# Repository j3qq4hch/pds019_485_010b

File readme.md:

# pds019_485_010

В этом репозитории содержатся исходники проекта `pds019_485_010`. Проект включает в себя две платы: A и B.

На плате А располагается модуль esp32, разъемы для его программирования две кнопки и несколько светодиодов.

На плате B располагается система питания устройства, состоящая из AC-DC модуля, создающего шину питания 12в и DC-DC конвертера 12в -> 3.3в. Кроме этого на плате B располагается гальванически изолированный RS485 интерфейс, реле и разъем для подключения датчика. 

# Плата А

# Плата B
<p align = center>

| Сторона TOP  | Сторона BOTTOM |
|-------------|-----------|
|||

</p>

3D модель доступна [по ссылке](https://a360.co/4bcfLyz).
BoM доступен [по ссылке](https://docs.google.com/spreadsheets/d/1rppHGotYg97vevn0TNhSlOjf3by5jG4KPH9rv6CT_tg/edit?gid=943701483#gid=943701483).

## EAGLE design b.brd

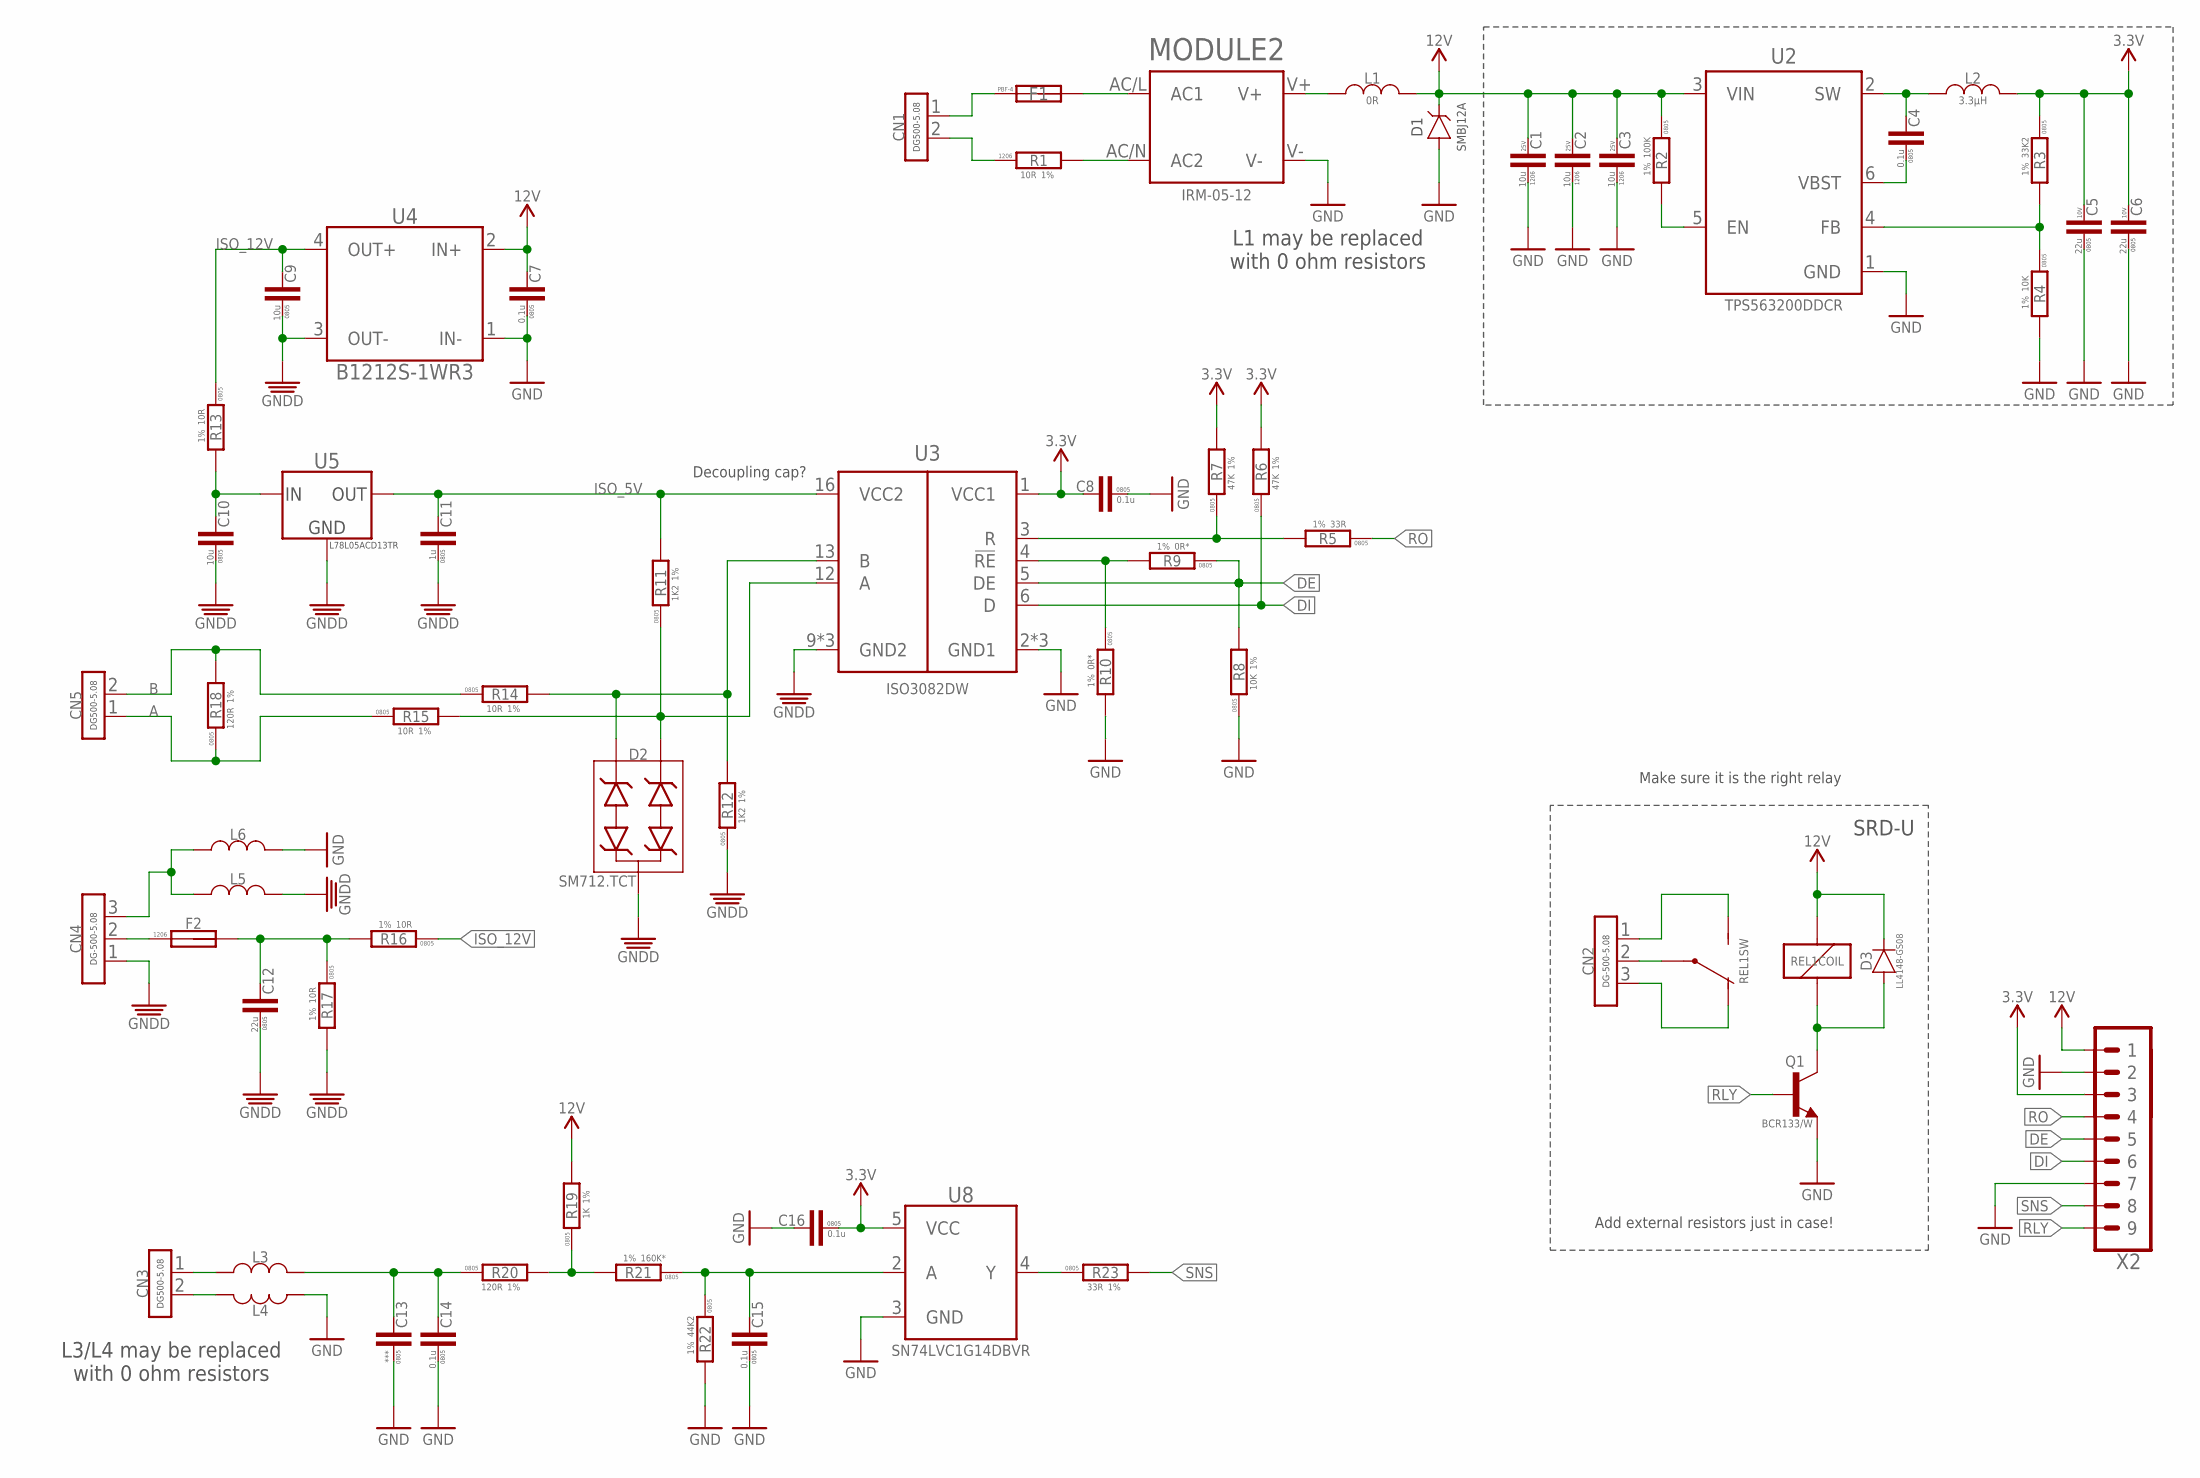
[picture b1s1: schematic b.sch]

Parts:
C1, C2, C3: 10u; C1206; VOLTAGE 25V
C4, C7, C8, C14, C15, C16: 0.1u; C0805
C5, C6: 22u; C0805; VOLTAGE 10V
C9, C10: 10u; C0805
C11: 1u; C0805
C12: 22u; C0805
C13: ***; C0805
CN1, CN3, CN5: CON-2P-DG500-5.08; DG500-5.08-02P
CN2, CN4: CON-3P-DG500-5.08; DG500-5.08-03P
D1: SMBJ12A-SMB; DO-214AA(SMB)
D2: SM712; SOT23B-3
D3: LL4148; LL-34
F1: 1.6A; MST-FUSE
F2: MF-NSMF050-2; F1206
L1: 0R; L0805
L2: 3.3µH; VLS6045EX
L3, L4, L5, L6: L-0805; L0805
MODULE2: IRM-05-12; IRM-05
Q1: BCR133; SOT23B-3
R1: 10R; R1206
R2: 100K; R0805
R3: 33K2; R0805
R4, R8: 10K; R0805
R5, R23: 33R; R0805
R6, R7: 47K; R0805
R9, R10: 0R*; R0805
R11, R12: 1K2; R0805
R13, R14, R15, R16, R17: 10R; R0805
R18, R20: 120R; R0805
R19: 1K; R0805
R21: 160K*; R0805
R22: 44K2; R0805
REL1: RELAY_SPDTHJR-3FF-SH; HJR-3FF-12VDC-S-Z
U2: TPS563200; SOT23-6
U3: ISO3082; SO-16W
U4: B1212S-1WR3; SIP-4
U5: L78L05ACD13TR; SOIC8
U8: 74LVC1G14DBV; SOT23-5
X2: PINHEAD_1X09-2.54-TH-MALE; 1X09-PTH-2.54

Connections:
3490587: R5.2, R7.1, U3.3 (R)
+12V: CN4.2, F2.P$1 (1)
A: CN5.1, R15.1, R18.1
B: CN5.2, R14.1, R18.2
DE: R8.2, R9.1, U3.5 (DE), X2.5
DI: R6.1, U3.6 (D), X2.6
GND: C1.P$1 (1), C2.P$1 (1), C3.P$1 (1), C5.1, C6.1, C7.1, C8.1, C13.1, C14.1, C15.1, C16.2, D1.A, L4.2, L6.1, MODULE2.V-, Q1.2 (E), R4.2, R8.1, R10.2, R22.2, U2.1 (GND), U3.2 (GND1), U3.7 (GND1), U3.8 (GND1), U4.1 (IN-), U8.3 (GND), X2.2, X2.7
GNDD: C9.1, C10.1, C11.1, C12.1, CN4.1, D2.3, L5.2, R12.1, R17.2, U3.9 (GND2), U3.10 (GND2), U3.15 (GND2), U4.3 (OUT-), U5.2 (GND), U5.3 (GND), U5.6 (GND), U5.7 (GND)
ISO_5V: C11.2, R11.2, U3.16 (VCC2), U5.1 (OUT)
ISO_12V: C9.2, R13.1, R16.1, U4.4 (OUT+)
unnamed: CN4.3, L5.1, L6.2
unnamed: MODULE2.AC/N (AC2), R1.P$2 (2)
unnamed: D2.2 (C2), R11.1, R15.2, U3.12 (A)
unnamed: D2.1 (C3), R12.2, R14.2, U3.13 (B)
unnamed: F1.2, MODULE2.AC/L (AC1)
unnamed: L1.1, MODULE2.V+
unnamed: C4.1, U2.6 (VBST)
unnamed: R9.2, R10.1, U3.4 (!RE)
unnamed: CN1.1, F1.1
unnamed: CN1.2, R1.P$1 (1)
unnamed: R2.2, U2.5 (EN)
unnamed: C4.2, L2.P$1 (1), U2.2 (SW)
unnamed: R3.2, R4.1, U2.4 (FB)
unnamed: CN2.2, REL1.1 (COM)
unnamed: CN2.3, REL1.4 (NC)
unnamed: CN2.1, REL1.3 (NO)
unnamed: CN3.1, L3.1
unnamed: CN3.2, L4.1
unnamed: C13.2, C14.2, L3.2, R20.1
unnamed: C10.2, R13.2, U5.8 (IN)
unnamed: R19.1, R20.2, R21.2
unnamed: C15.2, R21.1, R22.1, U8.2 (A)
unnamed: D3.A, Q1.3 (C), REL1.5 (2)
unnamed: R23.1, U8.4 (Y)
unnamed: C12.2, F2.P$2 (2), R16.2, R17.1
RLY: Q1.1 (B), X2.9
RO: R5.1, X2.4
SNS: R23.2, X2.8
VDD_3V3: C5.2, C6.2, C8.2, C16.1, L2.P$2 (2), R3.1, R6.2, R7.2, U3.1 (VCC1), U8.5 (VCC), X2.3
VDD_12V: C1.P$2 (2), C2.P$2 (2), C3.P$2 (2), C7.2, D1.C, D3.C, L1.2, R2.1, R19.2, REL1.2 (1), U2.3 (VIN), U4.2 (IN+), X2.1

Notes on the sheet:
Add external resistors just in case!
Make sure it is the right relay
Decoupling cap?
SRD-U
L3/L4 may be replaced with 0 ohm resistors
L1 may be replaced with 0 ohm resistors

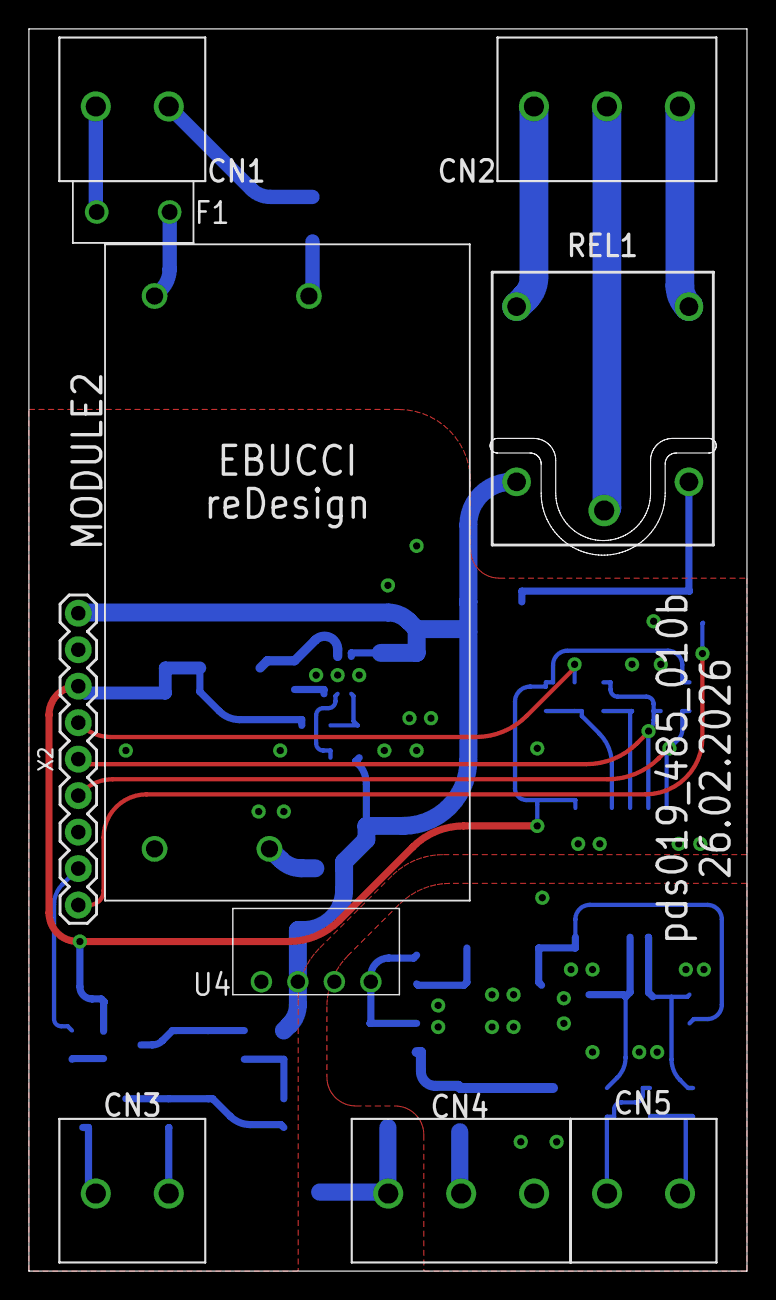
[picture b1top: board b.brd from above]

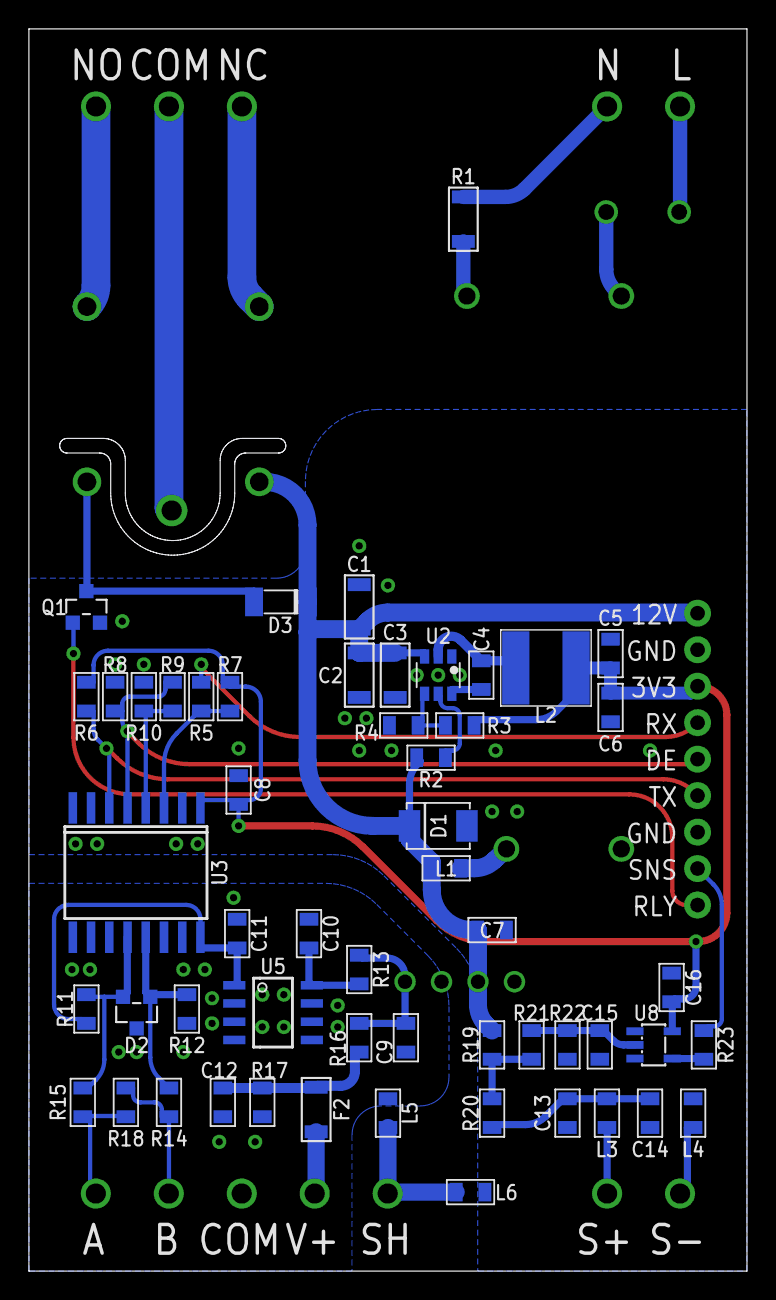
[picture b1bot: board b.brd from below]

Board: 2 copper layers, 50.0 x 86.5 mm, 65 parts (54 on the bottom side), 40 nets.

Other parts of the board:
U$1: REF_B

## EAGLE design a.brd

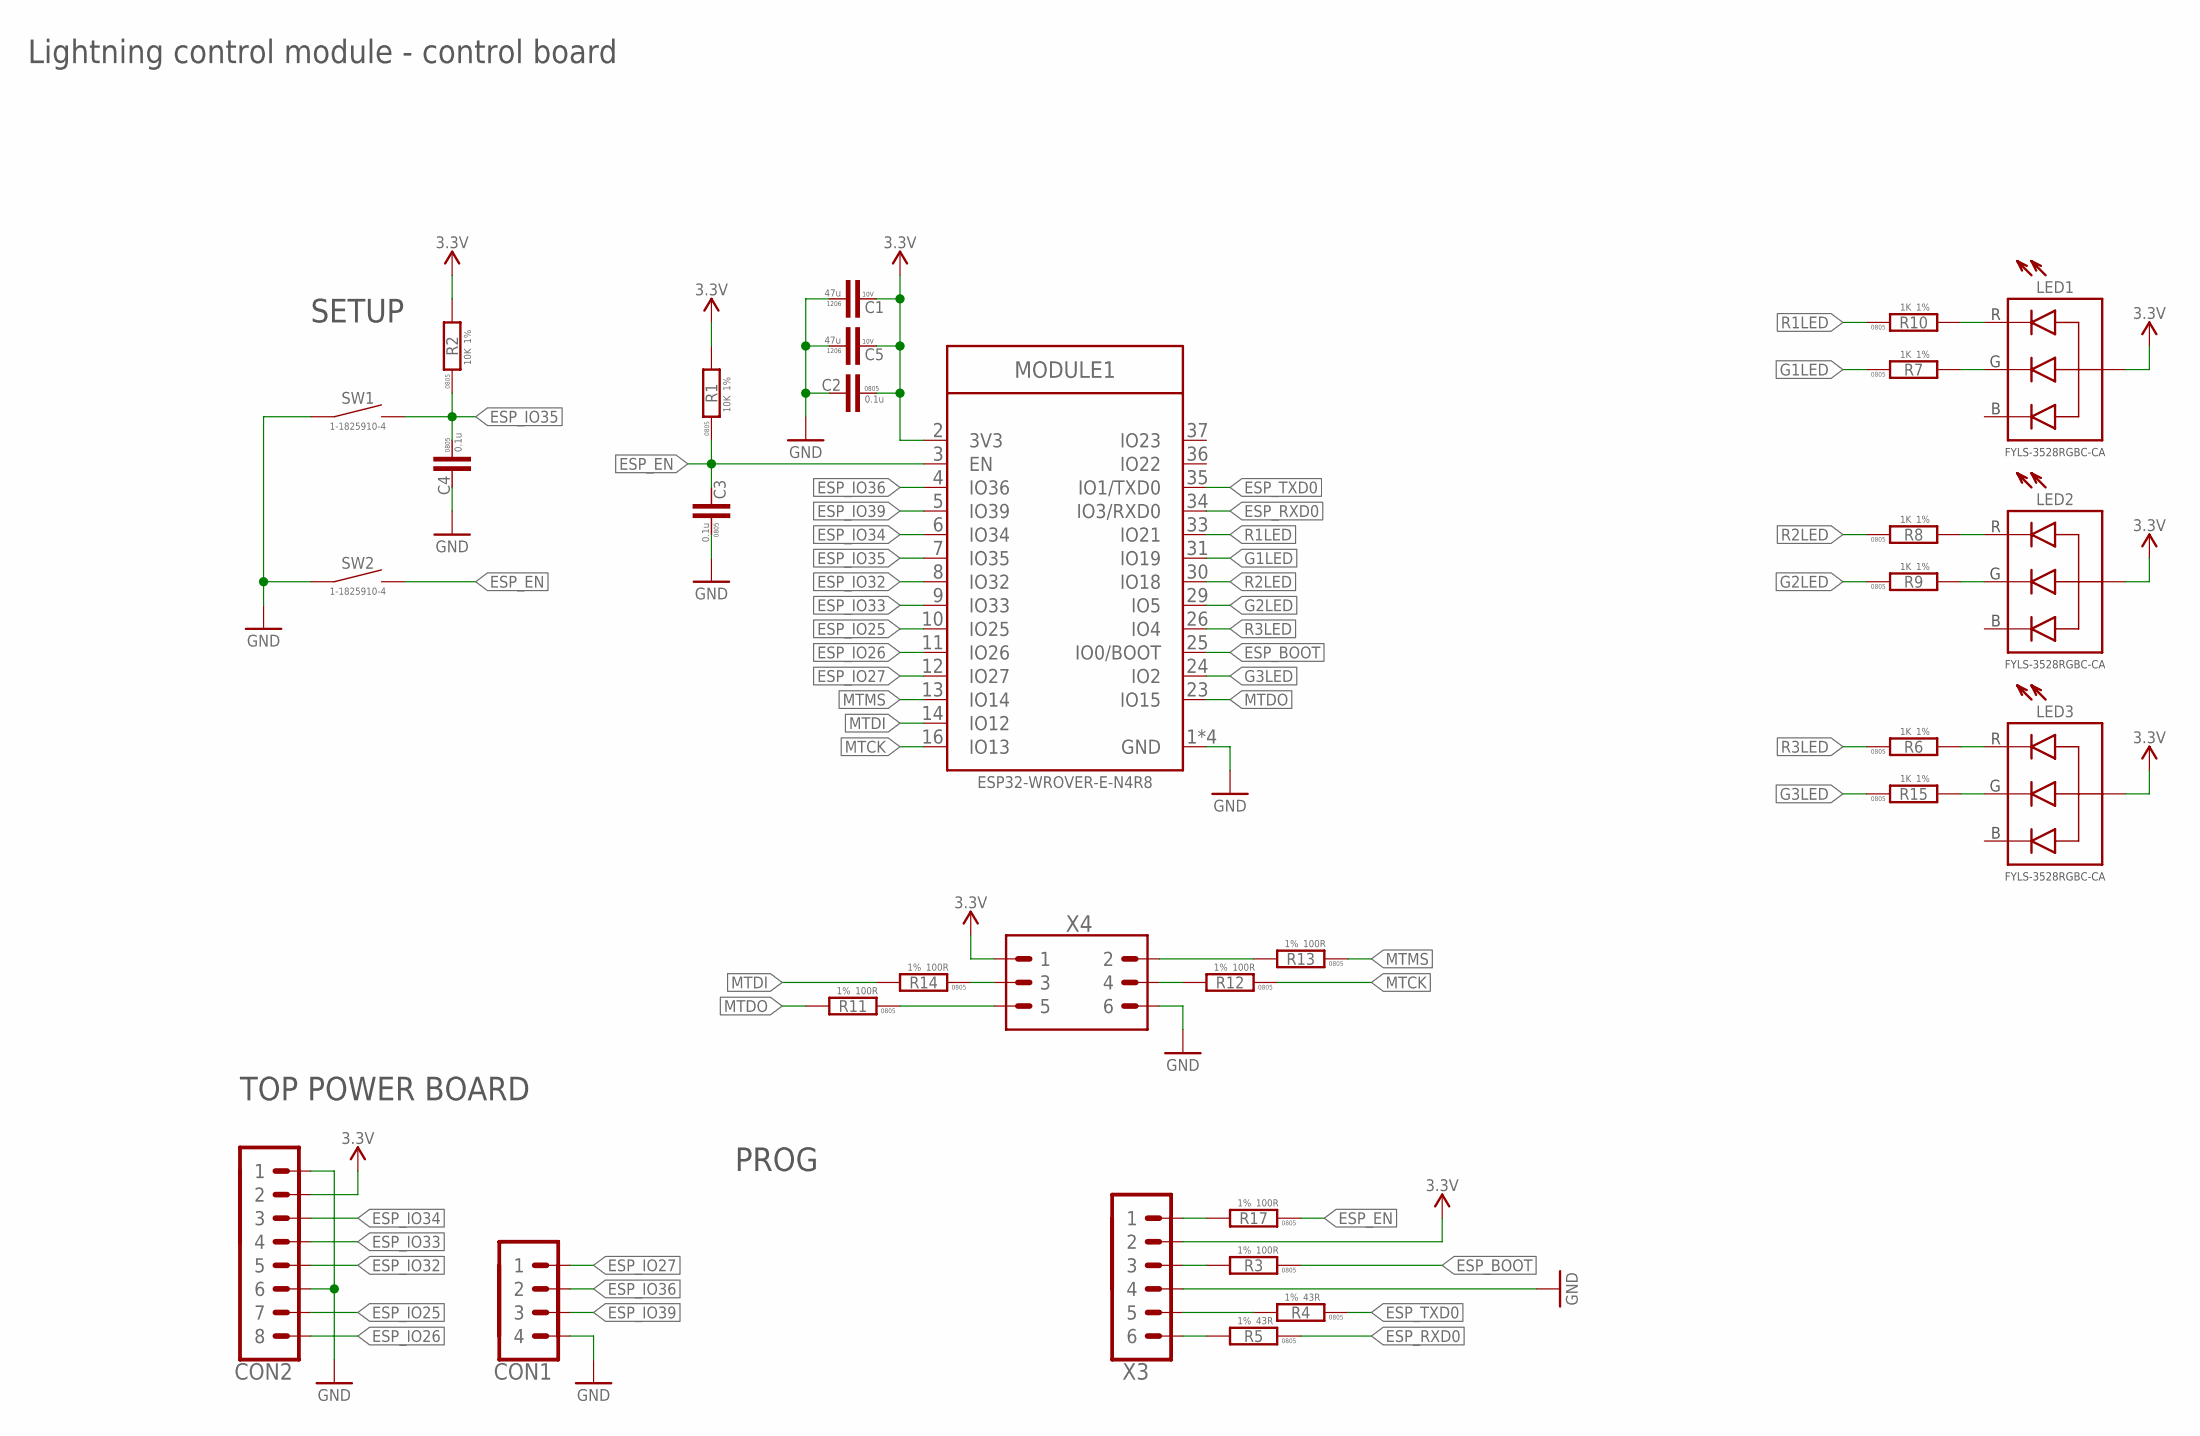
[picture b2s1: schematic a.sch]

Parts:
C1, C5: 47u; C1206; VOLTAGE 10V
C2, C3, C4: 0.1u; C0805
CON1: PINHEAD_1X04-2.54; 1X04-PTH-2.54
CON2: PINHEAD_1X08-2.54; 1X08-PTH-2.54
LED1, LED2, LED3: LED_RGB-3528; LED3528
MODULE1: ESP32-WROVER-(I)E; ESP32-WROVER-E
R1, R2: 10K; R0805
R3, R11, R12, R13, R14, R17: 100R; R0805
R4, R5: 43R; R0805
R6, R7, R8, R9, R10, R15: 1K; R0805
SW1, SW2: TACT_SWITCH-1-1825910-4; 1-1825910-4
X3: PINHEAD_1X06-2-MALE; 1X06-PTH-2
X4: PINHEAD_2X03-PTH-2.54; 2X03-PTH-2.54

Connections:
ESP_BOOT: MODULE1.25 (IO0/BOOT), R3.1
ESP_EN: C3.2, MODULE1.3 (EN), R1.1, R17.1, SW2.3 (2), SW2.4 (2)
ESP_IO25: CON2.7, MODULE1.10 (IO25)
ESP_IO26: CON2.8, MODULE1.11 (IO26)
ESP_IO27: CON1.1, MODULE1.12 (IO27)
ESP_IO32: CON2.5, MODULE1.8 (IO32)
ESP_IO33: CON2.4, MODULE1.9 (IO33)
ESP_IO34: CON2.3, MODULE1.6 (IO34)
ESP_IO35: C4.1, MODULE1.7 (IO35), R2.1, SW1.3 (2), SW1.4 (2)
ESP_IO36: CON1.2, MODULE1.4 (IO36)
ESP_IO39: CON1.3, MODULE1.5 (IO39)
ESP_RXD0: MODULE1.34 (IO3/RXD0), R5.1
ESP_TXD0: MODULE1.35 (IO1/TXD0), R4.1
G1LED: MODULE1.31 (IO19), R7.1
G2LED: MODULE1.29 (IO5), R9.1
G3LED: MODULE1.24 (IO2), R15.1
GND: C1.P$1 (1), C2.2, C3.1, C4.2, C5.P$1 (1), CON1.4, CON2.1, CON2.6, MODULE1.1 (GND), MODULE1.15 (GND), MODULE1.38 (GND), MODULE1.39 (GND), SW1.1, SW1.2 (1), SW2.1, SW2.2 (1), X3.4, X4.6
MTCK: MODULE1.16 (IO13), R12.1
MTDI: MODULE1.14 (IO12), R14.2
MTDO: MODULE1.23 (IO15), R11.2
MTMS: MODULE1.13 (IO14), R13.1
unnamed: LED2.1 (R), R8.2
unnamed: R13.2, X4.2
unnamed: R5.2, X3.6
unnamed: R4.2, X3.5
unnamed: R3.2, X3.3
unnamed: R12.2, X4.4
unnamed: LED1.1 (R), R10.2
unnamed: LED1.4 (G), R7.2
unnamed: LED2.4 (G), R9.2
unnamed: LED3.1 (R), R6.2
unnamed: LED3.4 (G), R15.2
unnamed: R14.1, X4.3
unnamed: R11.1, X4.5
unnamed: R17.2, X3.1
R1LED: MODULE1.33 (IO21), R10.1
R2LED: MODULE1.30 (IO18), R8.1
R3LED: MODULE1.26 (IO4), R6.1
VDD_3V3: C1.P$2 (2), C2.1, C5.P$2 (2), CON2.2, LED1.2 (A), LED2.2 (A), LED3.2 (A), MODULE1.2 (3V3), R1.2, R2.2, X3.2, X4.1

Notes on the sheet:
Lightning control module - control board
SETUP
PROG
TOP POWER BOARD

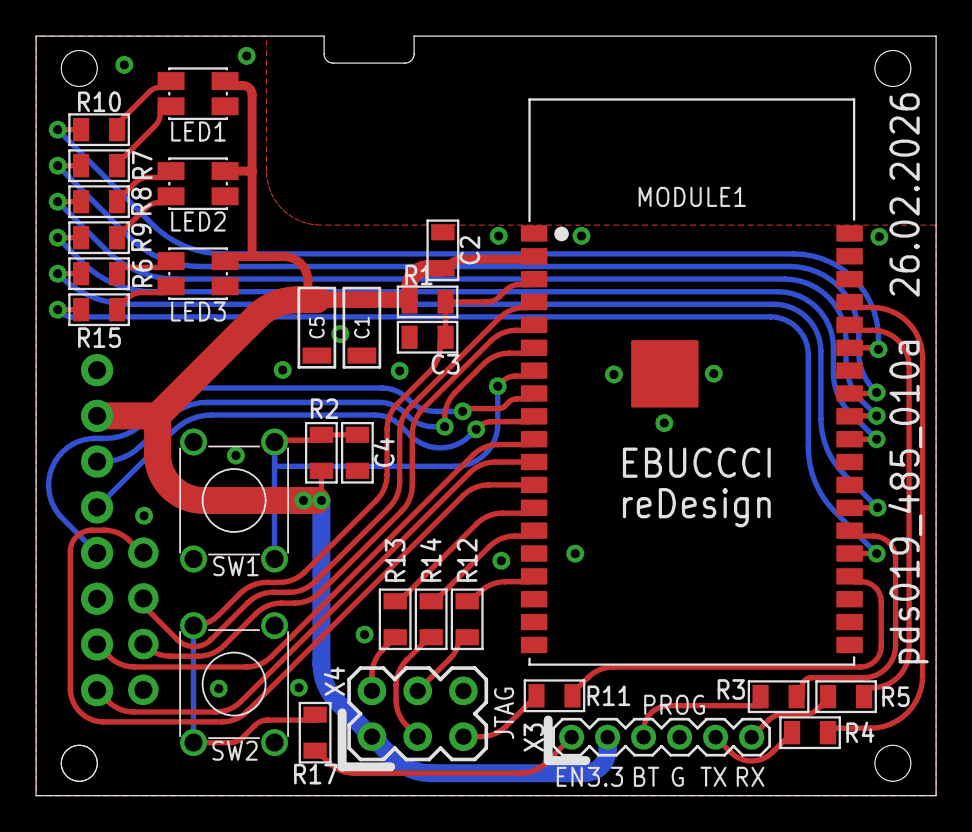
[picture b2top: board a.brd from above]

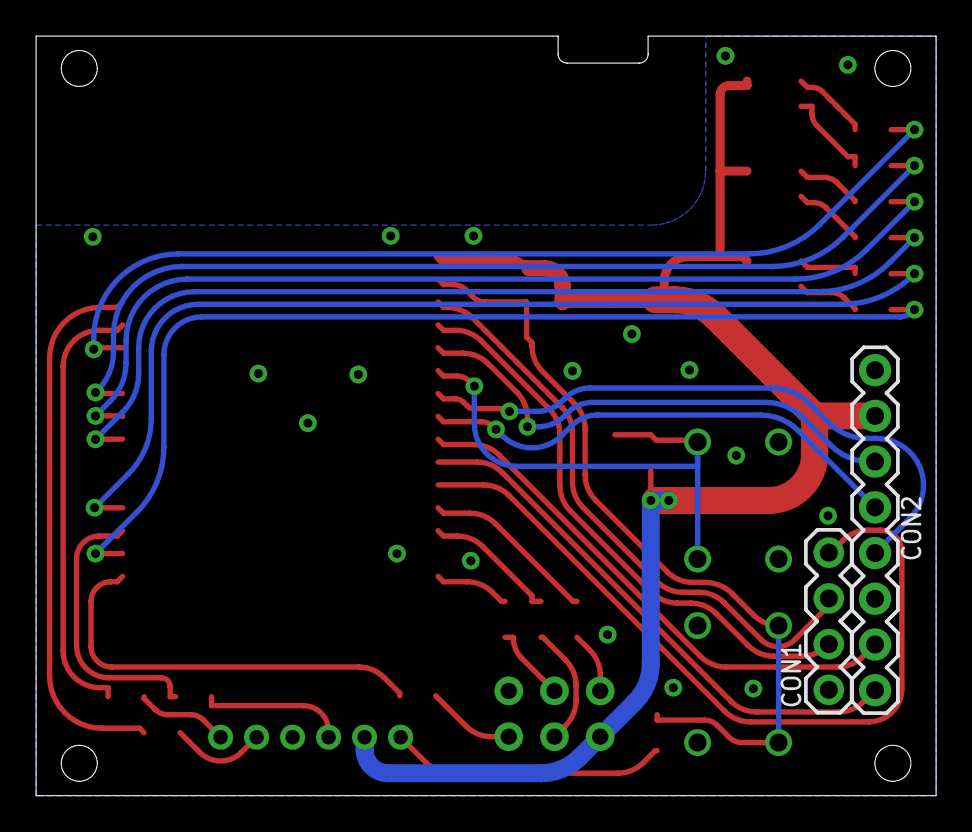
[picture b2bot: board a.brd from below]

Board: 2 copper layers, 50.0 x 42.2 mm, 32 parts (2 on the bottom side), 39 nets.

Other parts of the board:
U$1: REF_A

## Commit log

2026-03-02 notes
2026-03-03 preRelease minor fixes
2026-03-05 Notes and pictures update
